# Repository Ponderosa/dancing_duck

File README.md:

# Dancing Duck

This repo contains all software and tools for the Dancing Duck installation (title subject to change) for the Bumbershoot 2024 Festival. 

- Duck Firmware (Foundational work complete - RTOS, WiFi, MQTT Messaging, JSON interpretation, and Motor Control)
- Coordinator (Mosquitto is functionally passing motor command messages to duck)
- Monitor (No progress)

The design consists of ~20 motorized ducks that can be controlled to perform coordinated dance moves in the water. The ducks are decoys with an RC hobby boat mounted to the bottom. There are two DC brushed motor, each attached to a propeller. A custom PCBA will be manufactured that will feature the rPi Pico and a TI DRV33xx chip. The multicore RP2040 will be running SMP FreeRTOS and include LwIP and MQTT stacks. It will be able to interface with the Coordinator MQTT broker to receive motor commands, which will interface with a TI 83xx driver chip. Also included is a magnetometer to help ducks point in desired directions and to return to dock when needed.  

The ducks will be controlled via MQTT text based instructiones (JSON, G-Code, Something hand rolled?) being issued from the RPi4 Coordinator. The Coordinator will be running a broker, likely Mosquitto. Logging and monitoring infrastructure will be running on the Coordinator and may be accessed via a touchscreen mounted directly to the RPi4 or an external laptop known as the Monitor. 

# Duck Firmware
## Build Instructions
```
$ sudo apt update
$ sudo apt install cmake gcc-arm-none-eabi libnewlib-arm-none-eabi libstdc++-arm-none-eabi-newlib build-essential git
$ cd ~/workspace (or wherever you want to clone to)
$ git clone --recurse-submodules https://github.com/Ponderosa/dancing_duck.git
$ cd dancing_duck
$ git submodule update --init --recursive
$ cp wifi_example.sh wifi_secret.sh
$ vim wifi_secret.sh (add desired access point and MQTT broker information here)
$ ./build.sh <device_id>
```
Note: Please be careful not to commit any private wifi AP information.

For further Pico information, please see the getting started link below.

## Flashing Instructions
### Copy to mass storage via USB
The Pico can load firmware images by copying the U2F output file. It needs to put into mass storage mode first. To do this hold down the button on the pico while plugging in the USB cable. More instructions can be found in the getting started manual linked below.

### J-Link
1. Download and install latest package https://www.segger.com/downloads/jlink/ (Top section)
2. Solder 3 pins to Debug port on Pico and wire to SWD interface on J-Link.
3. Wire up hard reset pin to J-Link (Labeled "Run" on Pico)
4. Use flash.sh, ex `$ JLinkExe -ip 192.168.4.151 flash.sh`

### OpenOCD
Follow the getting started with Pico guide below.

## Debugging

### Serial Port
printf() is currently outputting to UART0 (GP0, GP1) at 3.3V. The UART is set to 115200-8-N-1. A lot of useful information is being streamed to this port. It is highly recommended to utilize this debug feature before venturing into GDB. 

Todo: Add build configuration file that can switch to USB CDC printf(). Or just move to USB CDC printf(). More details on CMakeLists modifications here: https://deepbluembedded.com/raspberry-pi-pico-serial-usb-c-sdk-serial-print-monitor/

### GDB
Since the rp2040 is dual core, care must be taken in properly attaching to the device. 

Included is a .vscode/launch.json to use with the VSCode plugin Cortex-Debug by marus25. Please feel free to add more configurations, as you probably don't have the same J-Link IP address I do. To get this to work start the Debug session directly from VSCode. You may need to reset the device one or two times with the left most reset button that appears in the new toolbar in the center top of VSCode. Once you do that, you should be able to use breakpoints and step through the code. 

Getting ARM GDB to run properly on Linux can be challenging. You may need to install older versions of libncurses and libncursesw

For my Ubuntu build this did the trick
```
sudo apt-get install libncurses5
sudo apt-get install libncursesw5
```

## Pico Documentation
- https://www.raspberrypi.com/documentation/microcontrollers/raspberry-pi-pico.html
- https://datasheets.raspberrypi.com/pico/getting-started-with-pico.pdf
- https://datasheets.raspberrypi.com/pico/raspberry-pi-pico-c-sdk.pdf
- https://datasheets.raspberrypi.com/rp2040/rp2040-datasheet.pdf

# Coordinator
1. Install https://mosquitto.org/download/ on RPi4.
2. edit `etc/mosquitto/conf.d/mosquitto.conf` and add 
```
allow_anonymous true
listener 1883 0.0.0.0
```
3. Run https://mqttx.app/ on any machine in the network for monitoring.

# MQTT Topics WIP
```
dancing_duck/
├── devices/
│   ├── {device_id}/
│   │   ├── sensors/
│   │   │   ├── temperature
│   │   │   ├── battery_voltage
│   │   │   └── ...
│   │   ├── metrics/
│   │   │   ├── freertos/
│   │   │   │   ├── heap
│   │   │   │   ├── tasks
│   │   │   │   └── ...
│   │   │   └── lwip
│   │   └── logs/
│   │   |   ├── info
│   │   |   ├── warning
│   │   |   └── error
│   │   └── command/
│   │   |   ├── motor
│   │   |   ├── navigate
│   │   |   ├── return_to_dock
│   │   |   ├── set_test_mode
│   │   |   └── ...
│   │   └── quack
│   └── ...
└── all_devices/
    ├── status
    └── command
        └── uart_tx
```

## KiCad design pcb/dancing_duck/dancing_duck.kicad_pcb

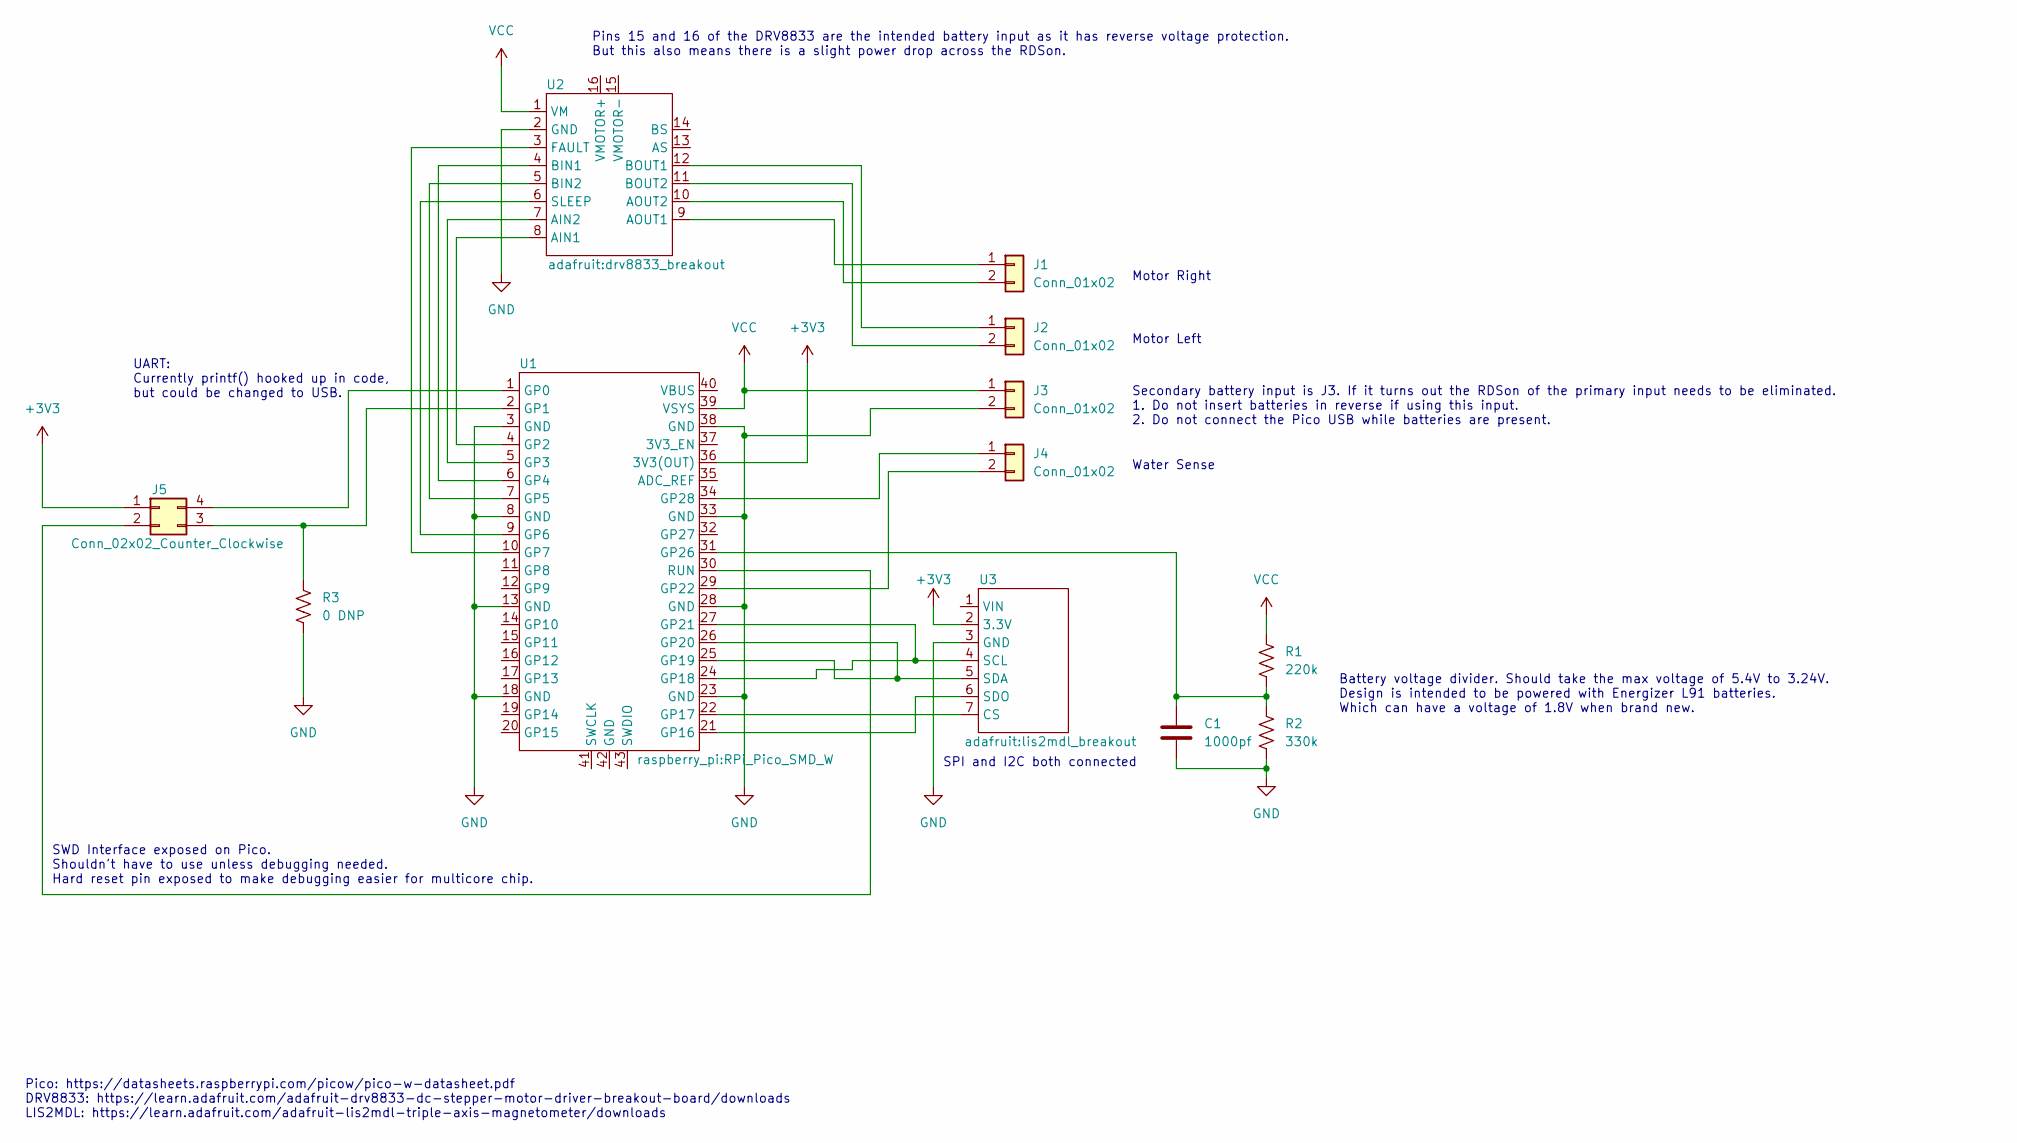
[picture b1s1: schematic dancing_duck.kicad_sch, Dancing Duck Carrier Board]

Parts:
C1: 1000pf; C_1206_3216Metric_Pad1.33x1.80mm_HandSolder; Part Num CL31B102KGFNNNE
J1, J2, J4: Conn_01x02; JST_PH_S2B-PH-K_1x02_P2.00mm_Horizontal
J3: Conn_01x02; TerminalBlock_Phoenix_PT-1,5-2-3.5-H_1x02_P3.50mm_Horizontal
J5: Conn_02x02_Counter_Clockwise; PinHeader_2x02_P2.54mm_Vertical
R1: 220k; R_1206_3216Metric_Pad1.30x1.75mm_HandSolder
R2: 330k; R_1206_3216Metric_Pad1.30x1.75mm_HandSolder
R3: 0 DNP; SolderJumper-2_P1.3mm_Open_TrianglePad1.0x1.5mm
U1: RPi_Pico_SMD_W
U2: drv8833_breakout
U3: lis2mdl_breakout

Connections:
+3V3: J5.1, U1.36 (3V3(OUT)), U3.2 (3.3V)
GND: C1.2, J3.2, R2.2, R3.2, U1.3 (GND), U1.8 (GND), U1.13 (GND), U1.18 (GND), U1.23 (GND), U1.28 (GND), U1.33 (GND), U1.38 (GND), U2.2 (GND), U3.3 (GND)
unnamed: J1.1, U2.9 (AOUT1)
unnamed: J1.2, U2.10 (AOUT2)
unnamed: J2.1, U2.12 (BOUT1)
unnamed: J2.2, U2.11 (BOUT2)
unnamed: J4.1, U1.34 (GP28)
unnamed: J4.2, U1.29 (GP22)
unnamed: J5.2, U1.30 (RUN)
unnamed: J5.3, R3.1, U1.2 (GP1)
unnamed: J5.4, U1.1 (GP0)
unnamed: U1.4 (GP2), U2.8 (AIN1)
unnamed: U1.5 (GP3), U2.7 (AIN2)
unnamed: U1.6 (GP4), U2.4 (BIN1)
unnamed: U1.7 (GP5), U2.5 (BIN2)
unnamed: U1.9 (GP6), U2.6 (SLEEP)
unnamed: U1.10 (GP7), U2.3 (FAULT)
unnamed: U1.21 (GP16), U3.6 (SDO)
unnamed: U1.22 (GP17), U3.7 (CS)
unnamed: U1.24 (GP18), U1.27 (GP21), U3.4 (SCL)
unnamed: U1.25 (GP19), U1.26 (GP20), U3.5 (SDA)
unnamed: C1.1, R1.2, R2.1, U1.31 (GP26)
VCC: J3.1, R1.1, U1.39 (VSYS), U2.1 (VM)

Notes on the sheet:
Motor Right
Motor Left
Secondary battery input is J3. If it turns out the RDSon of the primary input needs to be eliminated. 1. Do not insert batteries in reverse if using this input. 2. Do not connect the Pico USB while batteries are present.
Water Sense
Pico: https://datasheets.raspberrypi.com/picow/pico-w-datasheet.pdf DRV8833: https://learn.adafruit.com/adafruit-drv8833-dc-stepper-motor-driver-breakout-board/downloads LIS2MDL: https://learn.adafruit.com/adafruit-lis2mdl-triple-axis-magnetometer/downloads
Battery voltage divider. Should take the max voltage of 5.4V to 3.24V. Design is intended to be powered with Energizer L91 batteries. Which can have a voltage of 1.8V when brand new.
UART: Currently printf() hooked up in code, but could be changed to USB.
Pins 15 and 16 of the DRV8833 are the intended battery input as it has reverse voltage protection. But this also means there is a slight power drop across the RDSon.
SPI and I2C both connected
SWD Interface exposed on Pico. Shouldn't have to use unless debugging needed. Hard reset pin exposed to make debugging easier for multicore chip.

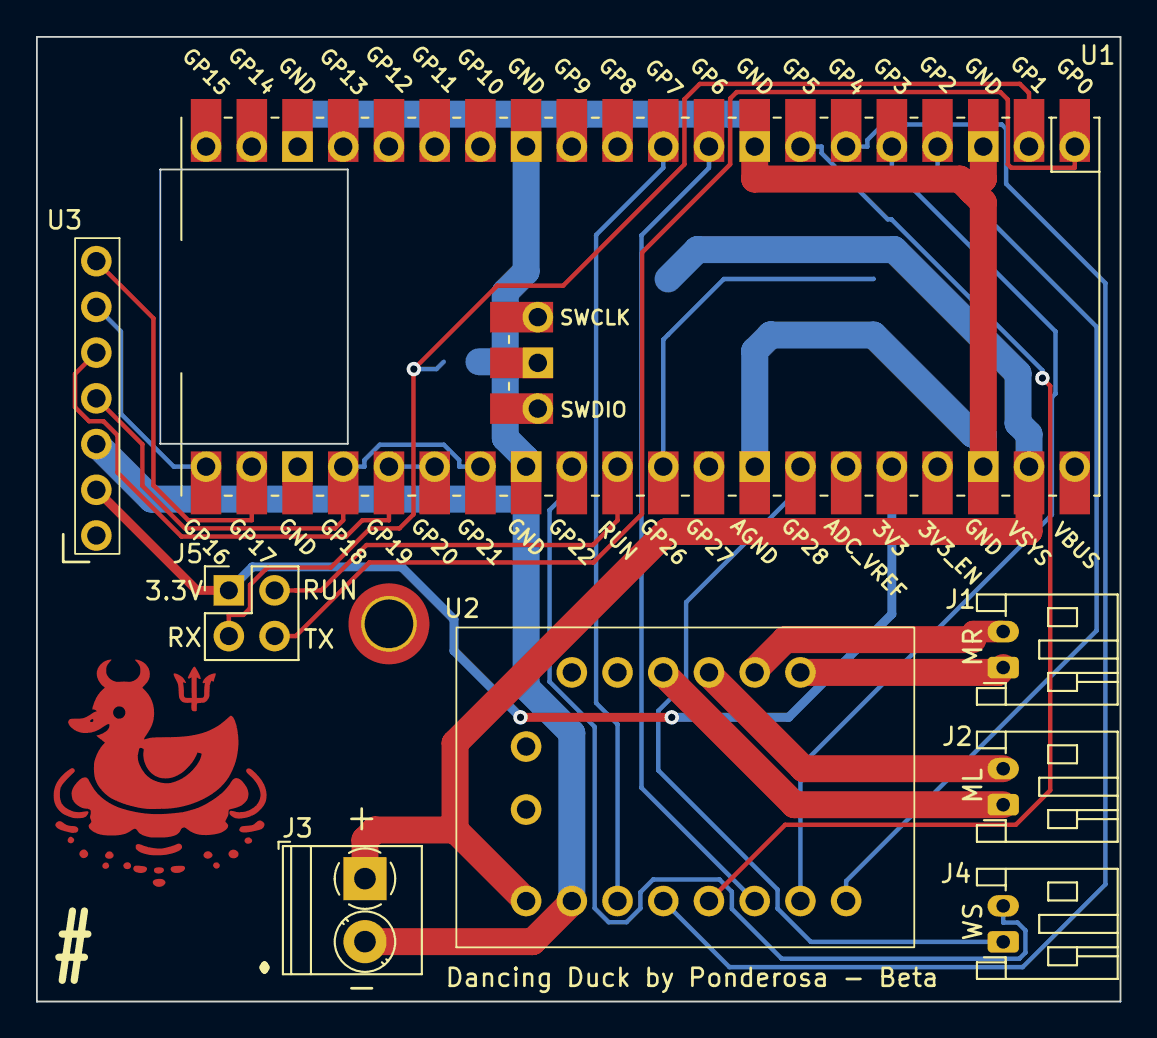
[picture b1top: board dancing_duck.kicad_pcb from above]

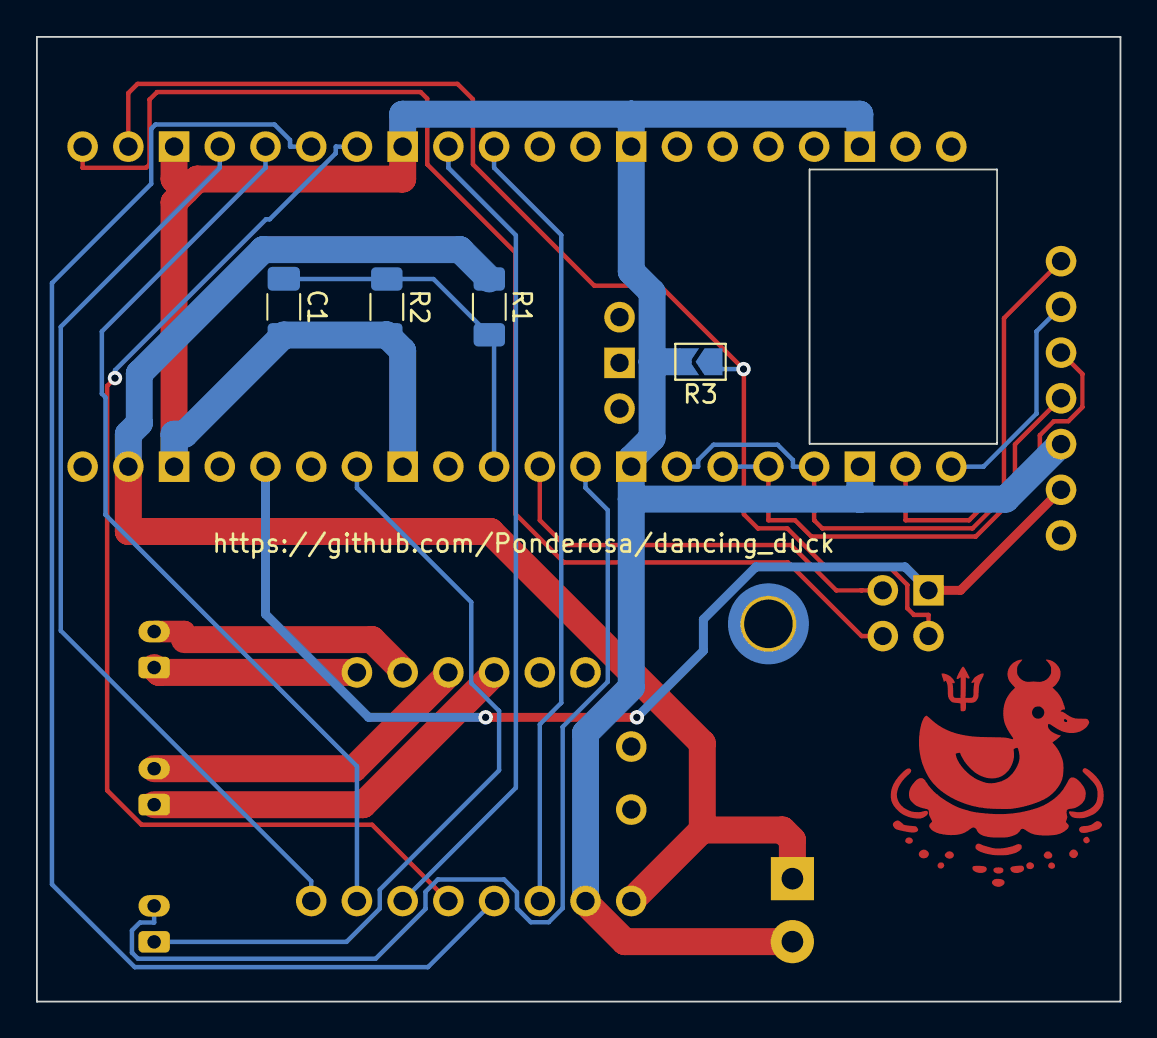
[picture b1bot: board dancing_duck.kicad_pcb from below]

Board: 2 copper layers, 60.2 x 53.6 mm, 14 parts (4 on the bottom side), 23 nets.

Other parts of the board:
G_LOGO: LOGO
REF1: MountingHole_2.7mm_M2.5_ISO14580_Pad_TopBottom

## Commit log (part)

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2024-06-07 feat: initial commit
    This is the first commit for the dancing_duck rp2040 embedded code for bumbershoot 2024.
    This code uses FreeRTOS to blink a light on the CWY wifi chip, and does a wifi scan for all local access points and prints it out on the UART0 pins.
    Next steps:
    - Get multicore GDB working
    - Add README
    - Get MQTT working with WLAN
2024-06-07 fix: GDB now working in VSCode
    Steps to debug:
    1. Update or comment out IP Address of J-Link probe
    2. Build and Flash firmware
    3. Attach each configuration
    4. Reset device with leftmost button in new toolbar.
    5. May need to reset device again after hitting a breakpoint or two, but after that should be good to go.
2024-06-09 build: mqtt now buildingin project
    todo: add mqtt test functionality
2024-06-09 fix: cwy43 wifi now using freertos
    problem: cwy code was not using freertos context. Now it is.
    note: cwy43 must be initialized in a FreeRTOS task
2024-06-09 refactor: cleanup header in main
2024-06-09 refactor: prep to add more wifi tasks
2024-06-10 build: add wifi secret env vars
2024-06-10 feat: add ping task
    testing: works by pinging google's 8.8.8.8
2024-06-10 refactor: add wifi task toggle
    wifi scan and ping cannout run at the same time. added toggle to easily allow switching between modes.
2024-06-12 feat: working MQTT pub and sub
    todo: clean up and add README
2024-06-15 fix: submodule folder needs to be added
2024-06-15 fix: remove coreMQTT from CMakeLists
2024-06-15 doc: add initial README
    Please update as needed, or let me know if you have any questions.
2024-06-15 doc: update README
2024-06-15 refactor: clean up wifi
    - move hardcoded MQTT IP address to config
    - make MQTT functions more service like
    - task creation is all local to each other again
    - add keep alive message
2024-06-16 feat: add unique ID to keep alive
2024-06-16 feat: add basic motor control
    Testing: with DRV8833 and DC motors on duck. Damaged one motor due to water splashing onto it.
    Project Next Steps:
    Test overall strategy by mounting electronics in duck and see how long a set of energizer lithium AA batteries last with duck spinning in circles in tub.
    Code next steps:
    Hook MQTT messaging directly to motor driver. Just allow it scale pwm duty cycle and frequency for each motor.
2024-06-16 feat: added FreeRTOS task status printing
    note: the debugger isn't aware of the FreeRTOS tasks due to it not understanding the new datastructure for SMP. Todo: look into finding a fix for this.
2024-06-16 feat: add cJSON
    also cleaned up CMakeLists.txt
    Todo: cleanup errors reported by new compiler options
2024-06-16 feat: JSON parsing for motor command
2024-06-17 feat: hookup mqtt to pwm
2024-06-17 cleanup: updat clang-format and run
    Testing:
    - Fresh build
    - Flash to device
    - Observe blink task
2024-06-17 refactor: motor.c
    - Remove magic numbers
    - Sanitize inputs
    - Add motor driver sleep functionality
    - Hook up duration
2024-06-17 fix: fix a few compiler warnings
2024-06-17 refactor: cleanup remaining warnings
2024-06-17 fix: intellisense
2024-06-17 refactor: move commanding up a level
2024-06-17 refactor: cleanup CMakeLists
2024-06-17 refactor: cleanup config and commanding
2024-06-17 Create LICENSE
2024-06-28 pcb: add first draft of pcb
2024-06-28 feat: add battery adc to pcb
2024-06-28 test: add simple mqtt test to make motors wiggle
2024-06-30 doc: update schematic
2024-06-30 feat: add watchdog
    testing: ensured we can make it through init. Added infinite loop to a higher priority tast to see if watchdog bit. And it did.
2024-06-30 chore: update gitignore
2024-06-30 chore: relax wdt
2024-07-06 feat: add magnetometer
2024-07-06 feat: add duck id num
2024-07-06 chore: add comment to lwipopts
2024-07-06 feat: add printf switch to lis2mdl
2024-07-06 doc: add rough draft of topic heirachy
2024-07-06 refactor: move mqtt publising to own module
2024-07-06 feat: add publish scheduler
2024-07-07 fix: update topic to design
2024-07-07 feat: add printf debug control to motor
2024-07-07 fix: use proper json for battery drain test
2024-07-07 feat: add mag_cal python script
2024-07-07 feat: add code to find offset for mag_cal
2024-07-07 feat: add more build and RTOS info
2024-07-07 chore: prep for wireless ota
2024-07-07 Add picowota submodule
2024-07-07 feat: add picowota
2024-07-08 feat: mqtt enter wota
    testing: tested multiple times with serial-flash tool
2024-07-11 fix: update pcb to beta
    - Fix daughter board pin hole size
    - Add better support for connecting J-Link
    - Update silkscreen
2024-07-12 fix: add capacitor to pcb
2024-07-12 fix: add switch for mirrored props
2024-07-12 fix: remove debug printf
2024-07-13 feat: add calibration for lis2mdl
2024-07-13 fix: update publish rates
2024-07-13 fix: prep for wet run
    need to be able to log into alternative wifi in field
2024-07-13 fix: prop mirror
2024-07-14 feat: add RPi4 server setup
2024-07-14 chore: clenaup python script names
2024-07-14 fix: increase wifi timeout for
    - needed after dedicated AP and OTA script complete
2024-07-14 chore: cleanup imports and fix file mode
2024-07-14 chore: update picowata submodule
    2 outstanding PRs on original repo. Using fork for now.
2024-07-14 chore: update cmake for new picowota commits
2024-07-14 feat: add ip address as arg for wota broker
2024-07-14 chore: cleanup server setup script
2024-07-14 fix: watchdog timeout too long
    shorten to less than 8333ms.
2024-07-15 feat: add RX to GND solder bridge to PCB
2024-07-20 fix: update drain down test
2024-07-20 refactor: prep motor.c for new algos
2024-07-20 feat: add new motor commands
2024-07-22 feat: setup mqtt->grafana pipeline
2024-07-23 feat: add show runner outline
    this is just a rough outline, and functionality has not been tested.
2024-07-23 chore: cleanup unused parts of telegraf.conf
2024-07-23 chore: turnoff motor debugging
2024-07-23 doc: update server readme
2024-07-24 chore: update show files
2024-07-25 fix: add device_id arg to mag_calibrate
2024-07-26 fix: update show files
2024-07-26 fix: deep copy and extra line removal
2024-07-26 hack: disable alternative networks
2024-07-26 chore: setup timing for testing
2024-07-26 fix: update watchdog logic
2024-07-26 chore: add calibration data
2024-07-26 feat: publish mac address on boot to mqtt
2024-07-27 fix: add retry to wota script
2024-07-27 fix: debugger ip changed
    using raspberry pi server now
2024-07-27 fix: remove alt network, add unique mqtt client id
2024-07-27 fix: heading calculation update due to orientation
2024-07-27 chore: reduce FreeRTOS heap as only 20% is being used right now
2024-07-27 fix: update calibration of duck 1
2024-07-29 fix: increase point deadbnad
2024-07-29 chore: update readme
2024-07-29 fix: cleanup shared resources
    bug: fixed use of stack variables being passed around as FreeRTOS parameters. Now they are on the heap.
    added: added command to dump motor buffer and immediately turn off motors.
2024-07-29 fix: improve sync of coordinator and ducks
2024-07-30 fix: fix network stability
2024-07-30 fix: add threadsafe gaurds for lwip calls to mqtt
2024-07-31 fix: add missing header
2024-07-31 feat: add mqtt publish metrics and reset
2024-07-31 fix: shorten mqtt buffer
    we will anlayze metrics in the future to see if this buffer is ever full
2024-07-31 doc: first pass at style guide
2024-07-31 format: format python files using black
2024-07-31 doc: update style guide
2024-07-31 refactor: refactor main.c to align with style guide
2024-07-31 chore: move lwipopts to same folder as other configs
2024-07-31 refactor: project config file
2024-07-31 refactor: update adc module based on style guide
2024-08-01 refactor: commadning module
2024-08-01 feat: add bad json count as metric
2024-08-01 feat: add more mqtt reset logic
2024-08-01 fix: const pointer in main.c
2024-08-01 refactor: update lis2mdl and magetometer modules
2024-08-01 refactor: motor module
2024-08-01 refactor: publish module
2024-08-01 feat: add confidence measures to mag_cal
2024-08-02 feat: add first grafana dashboard
    only rpi4 cpu temp is here, more to come soon
2024-08-03 feat: get auto cal of mag working
2024-08-03 fix: update telegraf.conf
    Update to work better with Grafana and MQTT
2024-08-03 feat: add kasa calibration to motors
2024-08-03 fix: increase Kasa RMSE
2024-08-03 feat: add mag fields to grafana
2024-08-03 chore: clean up interfaces for magnetometer
2024-08-04 chore: update telegraf config
2024-08-04 fix: intialization bug
2024-08-04 fix: mag cal counting bug
2024-08-04 feat: update grafana dashboard
    includes all duck metrics now
2024-08-05 feat: new wota for ubiquiti network
2024-08-05 fix: update dashboard
2024-08-05 fix: remove AP from rpi4
2024-08-06 feat: add launch and calibrate commands
2024-08-06 feat: add launch support to show
2024-08-06 fix: cleanup show scripts
2024-08-07 feat: complete return to dock
2024-08-08 feat: add more hard reboot reasons
2024-08-08 fix: limit max motor consumption
2024-08-08 fix: add 3.3V rail closer to RUN (Jumper together)
2024-08-08 fix: extend calibration time
2024-08-09 Update queue set counts
2024-08-10 fix: add lis2mdl reset recovery
    I'm guessing this is caused by EMF, but every once in a while the config registers reset on some of the devices.
2024-08-15 fix: bump up mqtt buffer
2024-08-17 chore: update config.json for show
2024-08-17 fix: update rmse limit for noisy environments
2024-08-20 fix: parse mac address correctly on linux
2024-08-20 fix: remove hardware reset from jlink
2024-08-20 fix: update grafana
2024-08-20 fix: add mid motor range
2024-08-21 feat: calibration through reset
    anytime there is a soft reset the magnetometer calibration will be saved in watchdog scratch registers.
    bug: fixed semaphore give bug. now only happens once.
2024-08-21 fix: raise retry count for wifi
2024-08-21 fix: remove old wota
2024-08-21 fix: count sync dances
    the simple prng does not play well with MOD numbers, and we want to keep the sync going across all ducks, so we will just cycle throug the dances. it is unlikely any of the audience will be paying at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
2024-08-22 feat: have launch use swim if calibrated
2024-08-22 feat: add duck modes
2024-08-22 feat: add return to dock to CLI
2024-08-22 feat: add more dances
2024-08-22 feat: add server time and fw ver metrics
2024-08-22 fix: update better strtoul and loggin
2024-08-22 feat: add motor fault counter
2024-08-23 fix: intialize reent datastructure
2024-08-23 feat: publish mqtt rx count
2024-08-23 chore: bump fw version
2024-08-23 feat: update grafana to include new metric
    also added descriptions for each graph
2024-08-23 fix: mqtt cli
2024-08-23 fix: mqtt messaging bug
2024-08-23 feat: make it so we dance more often
    - if we accidently reset, and we have calibration data, we should start dancing.
    - We don't need to wait for the sync clock. it will find the duck eventually
2024-08-23 chore: update fw version
2024-08-23 chore: update wdt freq
2024-08-23 chore: refactor magnetometer for better printing
2024-08-23 doc: add note
2024-08-23 fix: double promotion
2024-08-23 build: add more warning checks
2024-08-24 feat: add wind correction
    testing: not done on real device yet.
2024-08-26 fix: wind cli error
2024-08-27 fix: make dances bigger
2024-08-27 doc: first draft of runbook
